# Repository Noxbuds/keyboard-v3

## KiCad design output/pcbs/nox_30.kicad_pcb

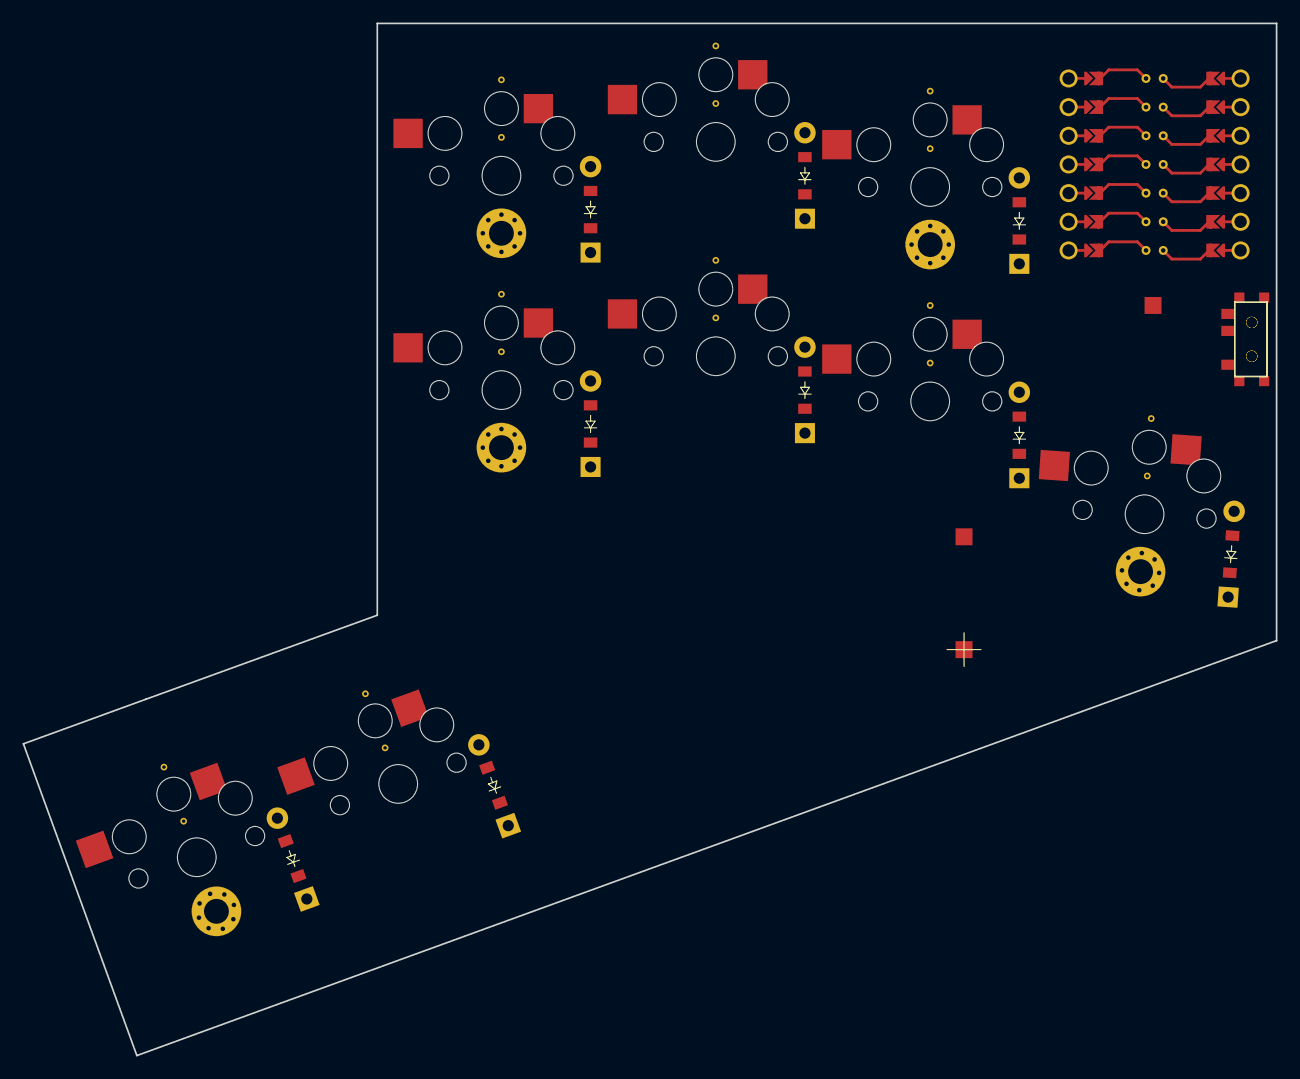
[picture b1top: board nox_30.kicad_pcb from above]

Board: 2 copper layers, 111.1 x 91.5 mm, 28 parts (0 on the bottom side), 19 nets, no tracks yet.

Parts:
BATTPAD1: ComboDiode
D1, D2, D3, D4, D5, D6, D7, D8, D9: ComboDiode
PAD1: SMDPad
S1, S2, S3, S4, S5, S6, S7, S8, S9: PG1350
T1, T2: SPDT_C128955
_19, _20, _21, _22, _23: MountingHole_2.2mm_M2_Pad_Via
xiao-ble1: ProMicro; xiao-ble

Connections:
BAT+: BATTPAD1.1, T1.1, T2.1
GND: BATTPAD1.2, xiao-ble1.2
P1: S1.2, S2.2, S8.2, xiao-ble1.23
P2: S3.2, S4.2, S9.2, xiao-ble1.22
P3: S5.2, S6.2, xiao-ble1.21
P4: S7.2, xiao-ble1.20
P8: D8.1, D9.1, xiao-ble1.6
P9: D1.1, D3.1, D5.1, D7.1, xiao-ble1.5
P10: D2.1, D4.1, D6.1, xiao-ble1.4
RAW: PAD1.1, T1.2, T2.2
index_home: D1.2, S1.1
index_top: D2.2, S2.1
middle_home: D3.2, S3.1
middle_top: D4.2, S4.1
one_main: D8.2, S8.1
pinky_home: D7.2, S7.1
ring_home: D5.2, S5.1
ring_top: D6.2, S6.1
two_main: D9.2, S9.1

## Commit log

2024-07-07 first version
2024-07-15 update gitignore
2024-07-15 18 key layout
2024-07-25 update case
